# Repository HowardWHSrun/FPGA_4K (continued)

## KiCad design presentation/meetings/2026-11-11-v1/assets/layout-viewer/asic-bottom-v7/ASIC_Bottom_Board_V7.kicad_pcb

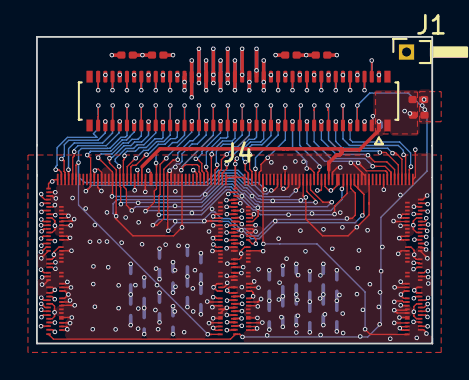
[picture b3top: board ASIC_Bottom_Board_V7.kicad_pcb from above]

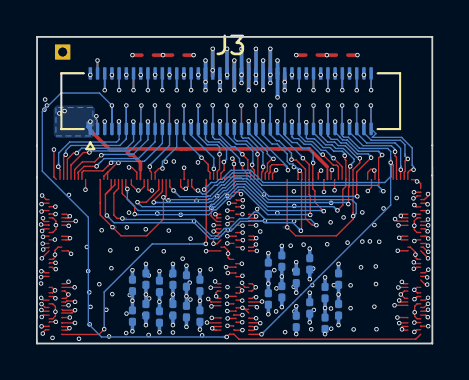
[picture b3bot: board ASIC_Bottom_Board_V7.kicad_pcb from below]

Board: 10 copper layers, 22.0 x 17.0 mm, 35 parts (25 on the bottom side), 78 nets.

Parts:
C1, C2, C4, C5, C6, C7, C14, C18, C19, C25, C26, C33, C34, C41, C42, C46, C48, C50, C51, C52, C53, C54, C55, C56, C57, C58, C59, C60, C61, C62: C_Small_US; C_0201_0603Metric
J1: Conn_01x01_Pin; PinHeader_1x01_P1.00mm_Horizontal
J3: Conn_02x40_Odd_Even; Hirose_DF40C-80DS-0.4V_2x40_P0.4mm
J4: Conn_02x40_Odd_Even; Hirose_DF40C-80DP-0.4V_2x40-1MP_P0.4mm
U01_BCD1, U01_BCD2: *; U01_BCD_OFF_CHIP

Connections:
/AC_IN: J3.69, J4.69, U01_BCD1.AC_IN, U01_BCD2.AC_IN
/AGND: C1.2, C2.2, C4.2, C5.2, C6.2, C18.2, C19.2, C25.2, C26.2, C33.2, C34.2, C41.2, C42.2, C46.2, C48.2, C50.2, C51.2, C52.2, C53.2, C54.2, C55.2, C56.2, C57.2, C58.2, C59.2, C60.2, J1.1 (Pin_1_1), J3.42, J3.44, J4.42, J4.44, U01_BCD1.AGND2, U01_BCD1.AGND_1, U01_BCD1.LAGND_1, U01_BCD1.LAGND_2, U01_BCD1.LAGND_3, U01_BCD1.LAGND_4, U01_BCD1.LAGND_5, U01_BCD1.LAGND_6, U01_BCD1.LAGND_7, U01_BCD1.LAGND_8, U01_BCD1.LAGND_9, U01_BCD1.LAGND_10, U01_BCD1.LAGND_11, U01_BCD1.LAGND_12, U01_BCD1.LAGND_13, U01_BCD1.LAGND_14, U01_BCD1.LAGND_15, U01_BCD1.LREF_GND1, U01_BCD1.LREF_GND2, U01_BCD1.LREF_GND3, U01_BCD1.LREF_GND4, U01_BCD1.RAGND_1, U01_BCD1.RAGND_2, U01_BCD1.RAGND_3, U01_BCD1.RAGND_4, U01_BCD1.RAGND_5, U01_BCD1.RAGND_6, U01_BCD1.RAGND_7, U01_BCD1.RAGND_8, U01_BCD1.RAGND_9, U01_BCD1.RAGND_10, U01_BCD1.RAGND_11, U01_BCD1.RAGND_12, U01_BCD1.RAGND_13, U01_BCD1.RAGND_14, U01_BCD1.RAGND_15, U01_BCD1.REF_1, U01_BCD1.REF_2, U01_BCD1.REF_3, U01_BCD1.REF_4, U01_BCD1.RREF_GND1, U01_BCD1.RREF_GND2, U01_BCD1.RREF_GND3, U01_BCD1.RREF_GND4, U01_BCD2.AGND2, U01_BCD2.AGND_1, U01_BCD2.LAGND_1, U01_BCD2.LAGND_2, U01_BCD2.LAGND_3, U01_BCD2.LAGND_4, U01_BCD2.LAGND_5, U01_BCD2.LAGND_6, U01_BCD2.LAGND_7, U01_BCD2.LAGND_8, U01_BCD2.LAGND_9, U01_BCD2.LAGND_10, U01_BCD2.LAGND_11, U01_BCD2.LAGND_12, U01_BCD2.LAGND_13, U01_BCD2.LAGND_14, U01_BCD2.LAGND_15, U01_BCD2.LREF_GND1, U01_BCD2.LREF_GND2, U01_BCD2.LREF_GND3, U01_BCD2.LREF_GND4, U01_BCD2.RAGND_1, U01_BCD2.RAGND_2, U01_BCD2.RAGND_3, U01_BCD2.RAGND_4, U01_BCD2.RAGND_5, U01_BCD2.RAGND_6, U01_BCD2.RAGND_7, U01_BCD2.RAGND_8, U01_BCD2.RAGND_9, U01_BCD2.RAGND_10, U01_BCD2.RAGND_11, U01_BCD2.RAGND_12, U01_BCD2.RAGND_13, U01_BCD2.RAGND_14, U01_BCD2.RAGND_15, U01_BCD2.REF_1, U01_BCD2.REF_2, U01_BCD2.REF_3, U01_BCD2.REF_4, U01_BCD2.RREF_GND1, U01_BCD2.RREF_GND2, U01_BCD2.RREF_GND3, U01_BCD2.RREF_GND4
/CHIP_RESET: J3.71, J4.71, U01_BCD1.RRST_DIGITAL, U01_BCD1.RST_DRIVER, U01_BCD2.RRST_DIGITAL, U01_BCD2.RST_DRIVER
/CLK32MHZ: J3.45, J4.45, U01_BCD1.CLK32MHZ
/CLK32MHZ(2): J3.19, J4.19, U01_BCD2.CLK32MHZ
/CLKH: J3.7, J4.7, U01_BCD1.CLKH, U01_BCD2.CLKH
/D<1>: J3.79, J4.79, U01_BCD1.DATAL<4>
/D<1>(2): J3.33, J4.33, U01_BCD2.DATAL<4>
/D<2>: J3.77, J4.77, U01_BCD1.DATAL<3>
/D<2>(2): J3.31, J4.31, U01_BCD2.DATAL<3>
/D<3>: J3.75, J4.75, U01_BCD1.DATAL<2>
/D<3>(2): J3.29, J4.29, U01_BCD2.DATAL<2>
/D<4>: J3.73, J4.73, U01_BCD1.DATAL<1>
/D<4>(2): J3.27, J4.27, U01_BCD2.DATAL<1>
/D<5>: J3.43, J4.43, U01_BCD1.DATAR<4>
/D<5>(2): J3.17, J4.17, U01_BCD2.DATAR<4>
/D<6>: J3.41, J4.41, U01_BCD1.DATAR<3>
/D<6>(2): J3.15, J4.15, U01_BCD2.DATAR<3>
/D<7>: J3.39, J4.39, U01_BCD1.DATAR<2>
/D<7>(2): J3.13, J4.13, U01_BCD2.DATAR<2>
/D<8>: J3.37, J4.37, U01_BCD1.DATAR<1>
/D<8>(2): J3.11, J4.11, U01_BCD2.DATAR<1>
/DGND: C7.2, C14.2, C61.2, C62.2, J3.46, J3.48, J4.46, J4.48, U01_BCD1.DGND1, U01_BCD1.DGND2, U01_BCD1.DGND3, U01_BCD1.DGND4, U01_BCD1.EN_LDO, U01_BCD1.LDGND_1, U01_BCD1.LDGND_2, U01_BCD1.LDGND_3, U01_BCD1.LDGND_4, U01_BCD1.LDGND_5, U01_BCD1.LDGND_6, U01_BCD1.LDGND_7, U01_BCD1.LDGND_8, U01_BCD1.LDGND_9, U01_BCD1.LDGND_10, U01_BCD1.LDGND_11, U01_BCD1.LDGND_12, U01_BCD1.LDGND_13, U01_BCD1.RDGND_1, U01_BCD1.RDGND_2, U01_BCD1.RDGND_3, U01_BCD1.RDGND_4, U01_BCD1.RDGND_5, U01_BCD1.RDGND_6, U01_BCD1.RDGND_7, U01_BCD1.RDGND_8, U01_BCD1.RDGND_9, U01_BCD1.RDGND_10, U01_BCD1.RDGND_11, U01_BCD1.RDGND_12, U01_BCD1.RDGND_13, U01_BCD2.DGND1, U01_BCD2.DGND2, U01_BCD2.DGND3, U01_BCD2.DGND4, U01_BCD2.EN_LDO, U01_BCD2.LDGND_1, U01_BCD2.LDGND_2, U01_BCD2.LDGND_3, U01_BCD2.LDGND_4, U01_BCD2.LDGND_5, U01_BCD2.LDGND_6, U01_BCD2.LDGND_7, U01_BCD2.LDGND_8, U01_BCD2.LDGND_9, U01_BCD2.LDGND_10, U01_BCD2.LDGND_11, U01_BCD2.LDGND_12, U01_BCD2.LDGND_13, U01_BCD2.RDGND_1, U01_BCD2.RDGND_2, U01_BCD2.RDGND_3, U01_BCD2.RDGND_4, U01_BCD2.RDGND_5, U01_BCD2.RDGND_6, U01_BCD2.RDGND_7, U01_BCD2.RDGND_8, U01_BCD2.RDGND_9, U01_BCD2.RDGND_10, U01_BCD2.RDGND_11, U01_BCD2.RDGND_12, U01_BCD2.RDGND_13
/DISC_OUT: J3.5, J4.5
/DISC_OUT(2): J3.3, J4.3
/DVDD: C7.1, C14.1, C61.1, C62.1, J3.34, J4.34, U01_BCD1.CGEN_RST, U01_BCD1.LDVDD_B1, U01_BCD1.LDVDD_B2, U01_BCD1.LDVDD_B3, U01_BCD1.LDVDD_T1, U01_BCD1.LDVDD_T2, U01_BCD1.LDVDD_T3, U01_BCD1.RDVDD_B1, U01_BCD1.RDVDD_B2, U01_BCD1.RDVDD_B3, U01_BCD1.RDVDD_T1, U01_BCD1.RDVDD_T2, U01_BCD1.RDVDD_T3, U01_BCD1.SPI_LDO_O, U01_BCD1.SPI_LDO_P, U01_BCD1.SPI_LDO_P1, U01_BCD1.SPI_LDO_P2, U01_BCD2.CGEN_RST, U01_BCD2.LDVDD_B1, U01_BCD2.LDVDD_B2, U01_BCD2.LDVDD_B3, U01_BCD2.LDVDD_T1, U01_BCD2.LDVDD_T2, U01_BCD2.LDVDD_T3, U01_BCD2.RDVDD_B1, U01_BCD2.RDVDD_B2, U01_BCD2.RDVDD_B3, U01_BCD2.RDVDD_T1, U01_BCD2.RDVDD_T2, U01_BCD2.RDVDD_T3, U01_BCD2.SPI_LDO_O, U01_BCD2.SPI_LDO_P, U01_BCD2.SPI_LDO_P1, U01_BCD2.SPI_LDO_P2
/FE_RESET: J3.65, J4.65, U01_BCD1.RST_FEL, U01_BCD1.RST_FER, U01_BCD2.RST_FEL, U01_BCD2.RST_FER
/IMP_TEST: J3.67, J4.67, U01_BCD1.IMP_TST, U01_BCD2.IMP_TST
/READ: J3.35, J4.35, U01_BCD1.READ
/READ(2): J3.9, J4.9, U01_BCD2.READ
/REF_VCM: C5.1, C46.1, C57.1, C58.1, J3.40, J4.40, U01_BCD1.LREF_VCM1, U01_BCD1.LREF_VCM2, U01_BCD1.LREF_VCM3, U01_BCD1.LREF_VCM4, U01_BCD1.RREF_VCM1, U01_BCD1.RREF_VCM2, U01_BCD1.RREF_VCM3, U01_BCD1.RREF_VCM4, U01_BCD1.VCM, U01_BCD2.LREF_VCM1, U01_BCD2.LREF_VCM2, U01_BCD2.LREF_VCM3, U01_BCD2.LREF_VCM4, U01_BCD2.RREF_VCM1, U01_BCD2.RREF_VCM2, U01_BCD2.RREF_VCM3, U01_BCD2.RREF_VCM4, U01_BCD2.VCM
/REF_VDD: C2.1, C33.1, C55.1, C56.1, J3.52, J4.52, U01_BCD1.LREF_VDD1, U01_BCD1.LREF_VDD2, U01_BCD1.LREF_VDD3, U01_BCD1.LREF_VDD4, U01_BCD1.RREF_VDD1, U01_BCD1.RREF_VDD2, U01_BCD1.RREF_VDD3, U01_BCD1.RREF_VDD4, U01_BCD2.LREF_VDD1, U01_BCD2.LREF_VDD2, U01_BCD2.LREF_VDD3, U01_BCD2.LREF_VDD4, U01_BCD2.RREF_VDD1, U01_BCD2.RREF_VDD2, U01_BCD2.RREF_VDD3, U01_BCD2.RREF_VDD4
/SPI_CLK: J3.63, J4.63, U01_BCD1.SPI_CLK, U01_BCD2.SPI_CLK
/SPI_DINL: J3.59, J4.59, U01_BCD1.SPI_DINL
/SPI_DINL(2): J3.25, J4.25, U01_BCD2.SPI_DINL
/SPI_DINR: J3.57, J4.57, U01_BCD1.SPI_DINR
/SPI_DINR(2): J3.23, J4.23, U01_BCD2.SPI_DINR
/SPI_LATCH: J3.61, J4.61, U01_BCD1.SPI_LATCH, U01_BCD2.SPI_LATCH
/STIM_CHB: J3.49, J4.49, U01_BCD1.FPGA_CHBL, U01_BCD1.FPGA_CHBR, U01_BCD2.FPGA_CHBL, U01_BCD2.FPGA_CHBR
/STIM_CLK: J3.53, J4.53, U01_BCD1.FPGA_CLK, U01_BCD2.FPGA_CLK
/STIM_EN: J3.51, J4.51, U01_BCD1.FPGA_EN, U01_BCD2.FPGA_EN
/STIM_START: J3.55, J4.55, U01_BCD1.FPGA_START, U01_BCD2.FPGA_START
/SYNC: J3.47, J4.47, U01_BCD1.SYNC
/SYNC(2): J3.21, J4.21, U01_BCD2.SYNC
/T_CLK32MHZ: J3.62, J4.62
/T_CLK32MHZ(2): J3.12, J4.12
/T_D<1>: J3.80, J4.80
/T_D<1>(2): J3.26, J4.26
/T_D<2>: J3.78, J4.78
/T_D<2>(2): J3.24, J4.24
/T_D<3>: J3.76, J4.76
/T_D<3>(2): J3.22, J4.22
/T_D<4>: J3.74, J4.74
/T_D<4>(2): J3.20, J4.20
/T_D<5>: J3.60, J4.60
/T_D<5>(2): J3.10, J4.10
/T_D<6>: J3.58, J4.58
/T_D<6>(2): J3.8, J4.8
/T_D<7>: J3.32, J4.32
/T_D<7>(2): J3.6, J4.6
/T_D<8>: J3.30, J4.30
/T_D<8>(2): J3.4, J4.4
/T_READ: J3.28, J4.28
/T_READ(2): J3.2, J4.2
/T_SPI_CLK: J3.72, J4.72
/T_SPI_DINL: J3.68, J4.68
/T_SPI_DINL(2): J3.18, J4.18
/T_SPI_DINR: J3.66, J4.66
/T_SPI_DINR(2): J3.16, J4.16
/T_SPI_LATCH: J3.70, J4.70
/T_SYNC: J3.64, J4.64
/T_SYNC(2): J3.14, J4.14
/VDD10: C18.1, C19.1, J3.36, J4.36, U01_BCD1.P10_L, U01_BCD1.P10_R, U01_BCD2.P10_L, U01_BCD2.P10_R
/VDD_ADC: C1.1, C34.1, C53.1, C54.1, J3.56, J4.56, U01_BCD1.LVDD_ADC1, U01_BCD1.LVDD_ADC2, U01_BCD1.LVDD_ADC3, U01_BCD1.LVDD_ADC4, U01_BCD1.LVDD_ADC5, U01_BCD1.RVDD_ADC1, U01_BCD1.RVDD_ADC2, U01_BCD1.RVDD_ADC3, U01_BCD1.RVDD_ADC4, U01_BCD1.RVDD_ADC5, U01_BCD2.LVDD_ADC1, U01_BCD2.LVDD_ADC2, U01_BCD2.LVDD_ADC3, U01_BCD2.LVDD_ADC4, U01_BCD2.LVDD_ADC5, U01_BCD2.RVDD_ADC1, U01_BCD2.RVDD_ADC2, U01_BCD2.RVDD_ADC3, U01_BCD2.RVDD_ADC4, U01_BCD2.RVDD_ADC5
/VDD_CGEN: C6.1, C50.1, J3.1, J4.1, U01_BCD1.VDD_CGEN, U01_BCD2.VDD_CGEN
/VDD_DRIVER: C41.1, C42.1, C59.1, C60.1, J3.38, J4.38, U01_BCD1.LVDD_DRIVER1, U01_BCD1.LVDD_DRIVER2, U01_BCD1.LVDD_DRIVER3, U01_BCD1.LVDD_DRIVER4, U01_BCD1.LVDD_DRIVER5, U01_BCD1.RVDD_DRIVER1, U01_BCD1.RVDD_DRIVER2, U01_BCD1.RVDD_DRIVER3, U01_BCD1.RVDD_DRIVER4, U01_BCD1.RVDD_DRIVER5, U01_BCD2.LVDD_DRIVER1, U01_BCD2.LVDD_DRIVER2, U01_BCD2.LVDD_DRIVER3, U01_BCD2.LVDD_DRIVER4, U01_BCD2.LVDD_DRIVER5, U01_BCD2.RVDD_DRIVER1, U01_BCD2.RVDD_DRIVER2, U01_BCD2.RVDD_DRIVER3, U01_BCD2.RVDD_DRIVER4, U01_BCD2.RVDD_DRIVER5
/VDD_FE: C4.1, C48.1, C51.1, C52.1, J3.50, J4.50, U01_BCD1.LVDD_FE1, U01_BCD1.LVDD_FE2, U01_BCD1.LVDD_FE3, U01_BCD1.LVDD_FE4, U01_BCD1.RVDD_FE1, U01_BCD1.RVDD_FE2, U01_BCD1.RVDD_FE3, U01_BCD1.RVDD_FE4, U01_BCD2.LVDD_FE1, U01_BCD2.LVDD_FE2, U01_BCD2.LVDD_FE3, U01_BCD2.LVDD_FE4, U01_BCD2.RVDD_FE1, U01_BCD2.RVDD_FE2, U01_BCD2.RVDD_FE3, U01_BCD2.RVDD_FE4
/VSS10: C25.1, C26.1, J3.54, J4.54, U01_BCD1.M10_L, U01_BCD1.M10_R, U01_BCD2.M10_L, U01_BCD2.M10_R
